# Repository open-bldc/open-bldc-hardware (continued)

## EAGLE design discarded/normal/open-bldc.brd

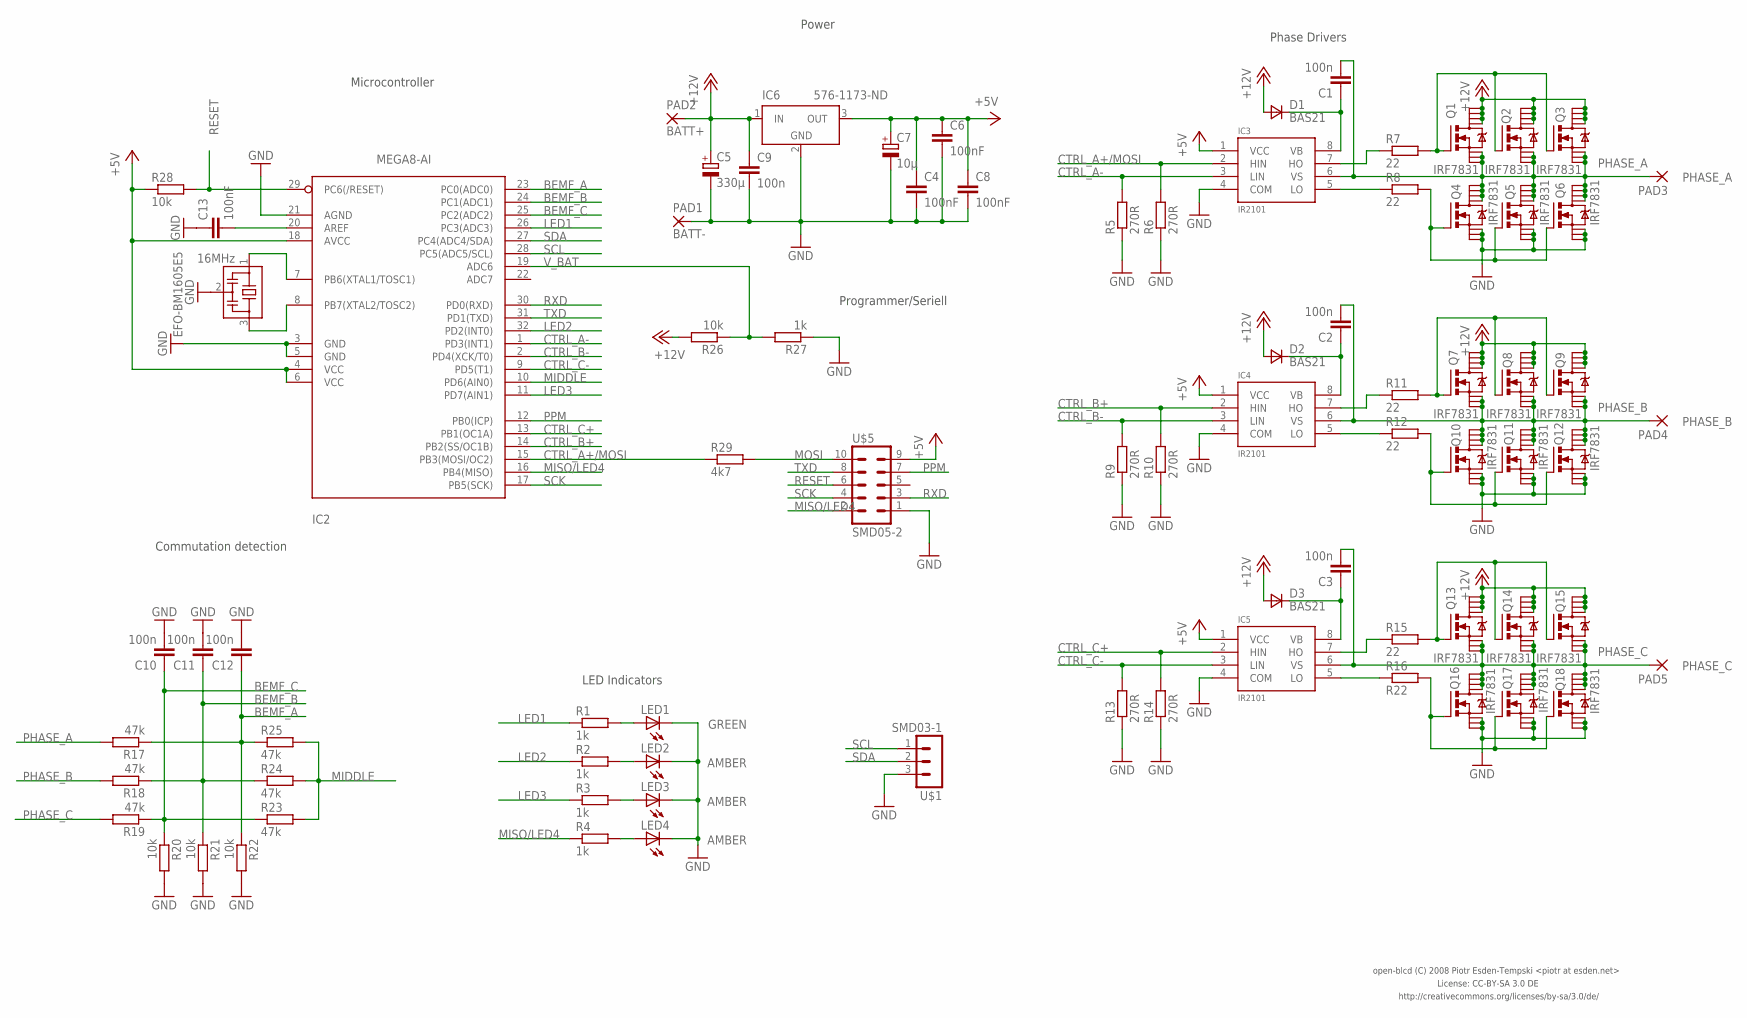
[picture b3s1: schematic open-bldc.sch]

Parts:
C1, C2, C3, C9, C10, C11, C12: 100n; C0603
C4, C6, C8, C13: 100nF; C0603
C5: 330µ; E3,5-8
C7: 10µ; D/7343-31R
D1, D2, D3: BAS21; SOT-23
EFO-BM1605E5: 16MHz; EFOBM
IC2: MEGA8-AI; TQFP32-08
IC3, IC4, IC5: IR2101; SO-8
IC6: 576-1173-ND; SOT223
LED1: GREEN; CHIP-LED0603
LED2, LED3, LED4: AMBER; CHIP-LED0603
PAD1: BATT-; SMD2,54-5,08
PAD2: BATT+; SMD2,54-5,08
PAD3: PHASE_A; SMD2,54-5,08
PAD4: PHASE_B; SMD2,54-5,08
PAD5: PHASE_C; SMD2,54-5,08
Q1, Q2, Q3, Q4, Q5, Q6, Q7, Q8, Q9, Q10, Q11, Q12, Q13, Q14, Q15, Q16, Q17, Q18: IRF7831; SO-08
R1, R2, R3, R4, R27: 1k; R0603
R5, R6, R9, R10, R13, R14: 270R; R0603
R7, R8, R11, R12, R15: 22; R0603
R16: R22; R0603
R17, R18, R19, R23, R24, R25: 47k; R0603
R20, R21, R22, R26, R28: 10k; R0603
R29: 4k7; R0603
U$1: SMD03-1
U$5: SMD05-2

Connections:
+5V: C4.1, C6.1, C7.+, C8.1, IC2.4 (VCC), IC2.6 (VCC), IC2.18 (AVCC), IC3.1 (VCC), IC4.1 (VCC), IC5.1 (VCC), IC6.3 (OUT), R28.1, U$5.9
+12V: C5.+, C9.1, D1.3 (A), D2.3 (A), D3.3 (A), IC6.1 (IN), PAD2.1, Q1.5 (D), Q1.6 (D), Q1.7 (D), Q1.8 (D), Q2.5 (D), Q2.6 (D), Q2.7 (D), Q2.8 (D), Q3.5 (D), Q3.6 (D), Q3.7 (D), Q3.8 (D), Q7.5 (D), Q7.6 (D), Q7.7 (D), Q7.8 (D), Q8.5 (D), Q8.6 (D), Q8.7 (D), Q8.8 (D), Q9.5 (D), Q9.6 (D), Q9.7 (D), Q9.8 (D), Q13.5 (D), Q13.6 (D), Q13.7 (D), Q13.8 (D), Q14.5 (D), Q14.6 (D), Q14.7 (D), Q14.8 (D), Q15.5 (D), Q15.6 (D), Q15.7 (D), Q15.8 (D), R26.2
BEMF_A: C12.1, IC2.23 (PC0(ADC0)), R17.1, R22.1, R25.1
BEMF_B: C11.1, IC2.24 (PC1(ADC1)), R18.1, R21.1, R24.1
BEMF_C: C10.1, IC2.25 (PC2(ADC2)), R19.1, R20.1, R23.1
CTRL_A+/MOSI: IC2.15 (PB3(MOSI/OC2)), IC3.2 (HIN), R6.2, R29.1
CTRL_A-: IC2.1 (PD3(INT1)), IC3.3 (LIN), R5.2
CTRL_B+: IC2.14 (PB2(SS/OC1B)), IC4.2 (HIN), R10.2
CTRL_B-: IC2.2 (PD4(XCK/T0)), IC4.3 (LIN), R9.2
CTRL_C+: IC2.13 (PB1(OC1A)), IC5.2 (HIN), R14.2
CTRL_C-: IC2.9 (PD5(T1)), IC5.3 (LIN), R13.2
GND: C4.2, C5.-, C6.2, C7.-, C8.2, C9.2, C10.2, C11.2, C12.2, C13.1, EFO-BM1605E5.2, IC2.3 (GND), IC2.5 (GND), IC2.21 (AGND), IC3.4 (COM), IC4.4 (COM), IC5.4 (COM), IC6.2 (GND), IC6.4 (GND), LED1.C, LED2.C, LED3.C, LED4.C, PAD1.1, Q4.1 (S), Q4.2 (S), Q4.3 (S), Q5.1 (S), Q5.2 (S), Q5.3 (S), Q6.1 (S), Q6.2 (S), Q6.3 (S), Q10.1 (S), Q10.2 (S), Q10.3 (S), Q11.1 (S), Q11.2 (S), Q11.3 (S), Q12.1 (S), Q12.2 (S), Q12.3 (S), Q16.1 (S), Q16.2 (S), Q16.3 (S), Q17.1 (S), Q17.2 (S), Q17.3 (S), Q18.1 (S), Q18.2 (S), Q18.3 (S), R5.1, R6.1, R9.1, R10.1, R13.1, R14.1, R20.2, R21.2, R22.2, R27.1, U$1.3, U$5.1
LED1: IC2.26 (PC3(ADC3)), R1.1
LED2: IC2.32 (PD2(INT0)), R2.1
LED3: IC2.11 (PD7(AIN1)), R3.1
MIDDLE: IC2.10 (PD6(AIN0)), R23.2, R24.2, R25.2
MISO/LED4: IC2.16 (PB4(MISO)), R4.1, U$5.2
MOSI: R29.2, U$5.10
unnamed: IC4.7 (HO), R11.1
unnamed: IC3.7 (HO), R7.1
unnamed: LED1.A, R1.2
unnamed: LED2.A, R2.2
unnamed: LED3.A, R3.2
unnamed: C13.2, IC2.20 (AREF)
unnamed: IC3.5 (LO), R8.1
unnamed: EFO-BM1605E5.1, IC2.7 (PB6(XTAL1/TOSC1))
unnamed: EFO-BM1605E5.3, IC2.8 (PB7(XTAL2/TOSC2))
unnamed: LED4.A, R4.2
unnamed: Q1.4 (G), Q2.4 (G), Q3.4 (G), R7.2
unnamed: C1.1, D1.1 (C), IC3.8 (VB)
unnamed: IC4.5 (LO), R12.1
unnamed: Q7.4 (G), Q8.4 (G), Q9.4 (G), R11.2
unnamed: Q4.4 (G), Q5.4 (G), Q6.4 (G), R8.2
unnamed: C2.1, D2.1 (C), IC4.8 (VB)
unnamed: Q10.4 (G), Q11.4 (G), Q12.4 (G), R12.2
unnamed: IC5.7 (HO), R15.1
unnamed: IC5.5 (LO), R16.1
unnamed: Q13.4 (G), Q14.4 (G), Q15.4 (G), R15.2
unnamed: C3.1, D3.1 (C), IC5.8 (VB)
unnamed: Q16.4 (G), Q17.4 (G), Q18.4 (G), R16.2
PHASE_A: C1.2, IC3.6 (VS), PAD3.1, Q1.1 (S), Q1.2 (S), Q1.3 (S), Q2.1 (S), Q2.2 (S), Q2.3 (S), Q3.1 (S), Q3.2 (S), Q3.3 (S), Q4.5 (D), Q4.6 (D), Q4.7 (D), Q4.8 (D), Q5.5 (D), Q5.6 (D), Q5.7 (D), Q5.8 (D), Q6.5 (D), Q6.6 (D), Q6.7 (D), Q6.8 (D), R17.2
PHASE_B: C2.2, IC4.6 (VS), PAD4.1, Q7.1 (S), Q7.2 (S), Q7.3 (S), Q8.1 (S), Q8.2 (S), Q8.3 (S), Q9.1 (S), Q9.2 (S), Q9.3 (S), Q10.5 (D), Q10.6 (D), Q10.7 (D), Q10.8 (D), Q11.5 (D), Q11.6 (D), Q11.7 (D), Q11.8 (D), Q12.5 (D), Q12.6 (D), Q12.7 (D), Q12.8 (D), R18.2
PHASE_C: C3.2, IC5.6 (VS), PAD5.1, Q13.1 (S), Q13.2 (S), Q13.3 (S), Q14.1 (S), Q14.2 (S), Q14.3 (S), Q15.1 (S), Q15.2 (S), Q15.3 (S), Q16.5 (D), Q16.6 (D), Q16.7 (D), Q16.8 (D), Q17.5 (D), Q17.6 (D), Q17.7 (D), Q17.8 (D), Q18.5 (D), Q18.6 (D), Q18.7 (D), Q18.8 (D), R19.2
PPM: IC2.12 (PB0(ICP)), U$5.7
RESET: IC2.29 (PC6(/RESET)), R28.2, U$5.6
RXD: IC2.30 (PD0(RXD)), U$5.3
SCK: IC2.17 (PB5(SCK)), U$5.4
SCL: IC2.28 (PC5(ADC5/SCL)), U$1.1
SDA: IC2.27 (PC4(ADC4/SDA)), U$1.2
TXD: IC2.31 (PD1(TXD)), U$5.8
V_BAT: IC2.19 (ADC6), R26.1, R27.2

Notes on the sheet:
Programmer/Seriell
Power
Microcontroller
Phase Drivers
License: CC-BY-SA 3.0 DE
http://creativecommons.org/licenses/by-sa/3.0/de/
LED Indicators
Commutation detection
open-blcd (C) 2008 Piotr Esden-Tempski <piotr at esden.net>

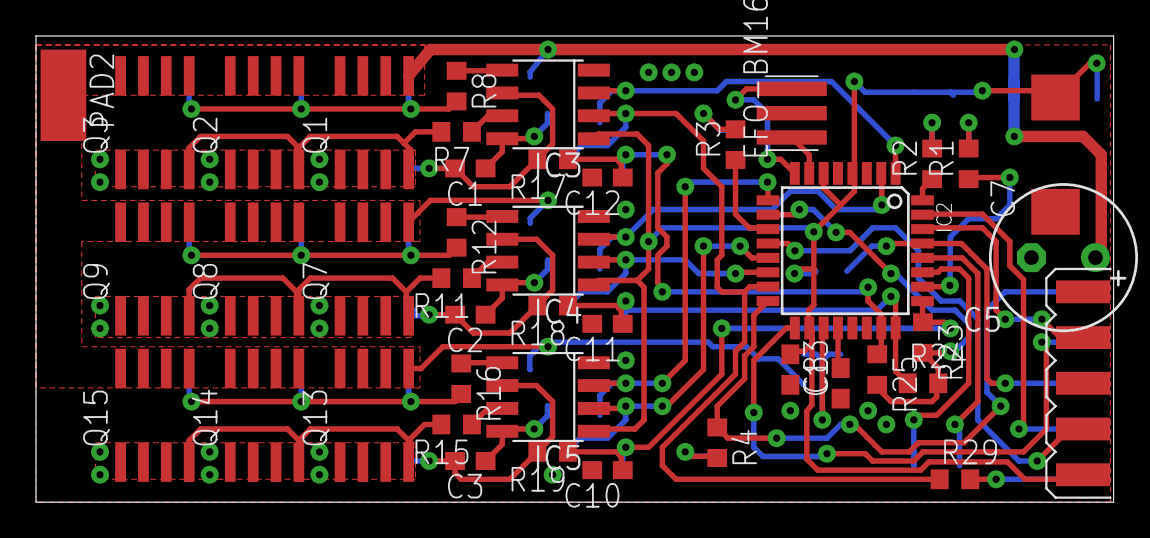
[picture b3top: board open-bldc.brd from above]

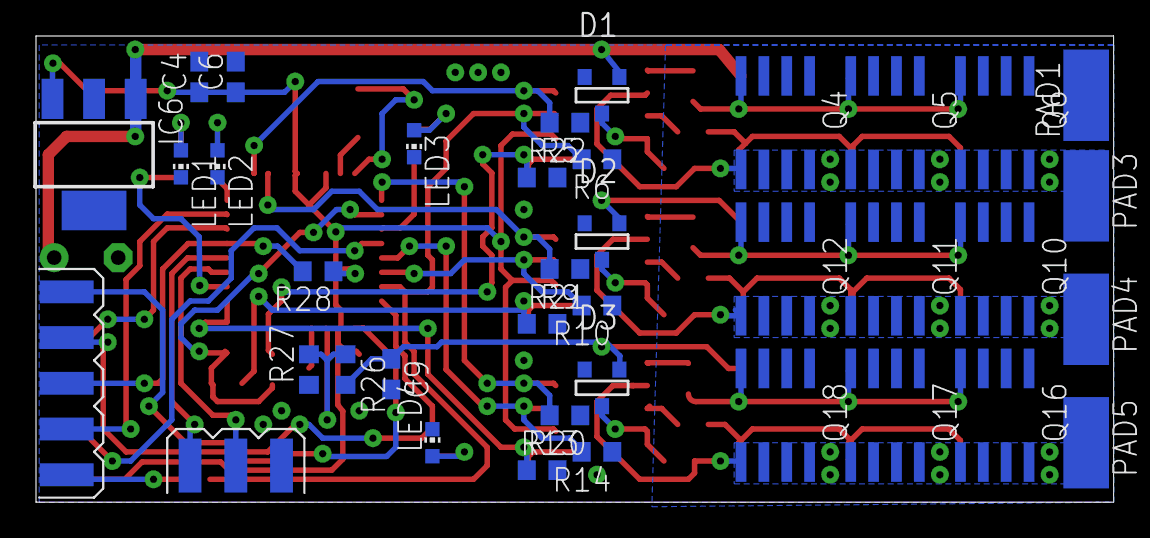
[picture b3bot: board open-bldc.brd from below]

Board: 2 copper layers, 59.9 x 25.9 mm, 80 parts (38 on the bottom side), 51 nets.

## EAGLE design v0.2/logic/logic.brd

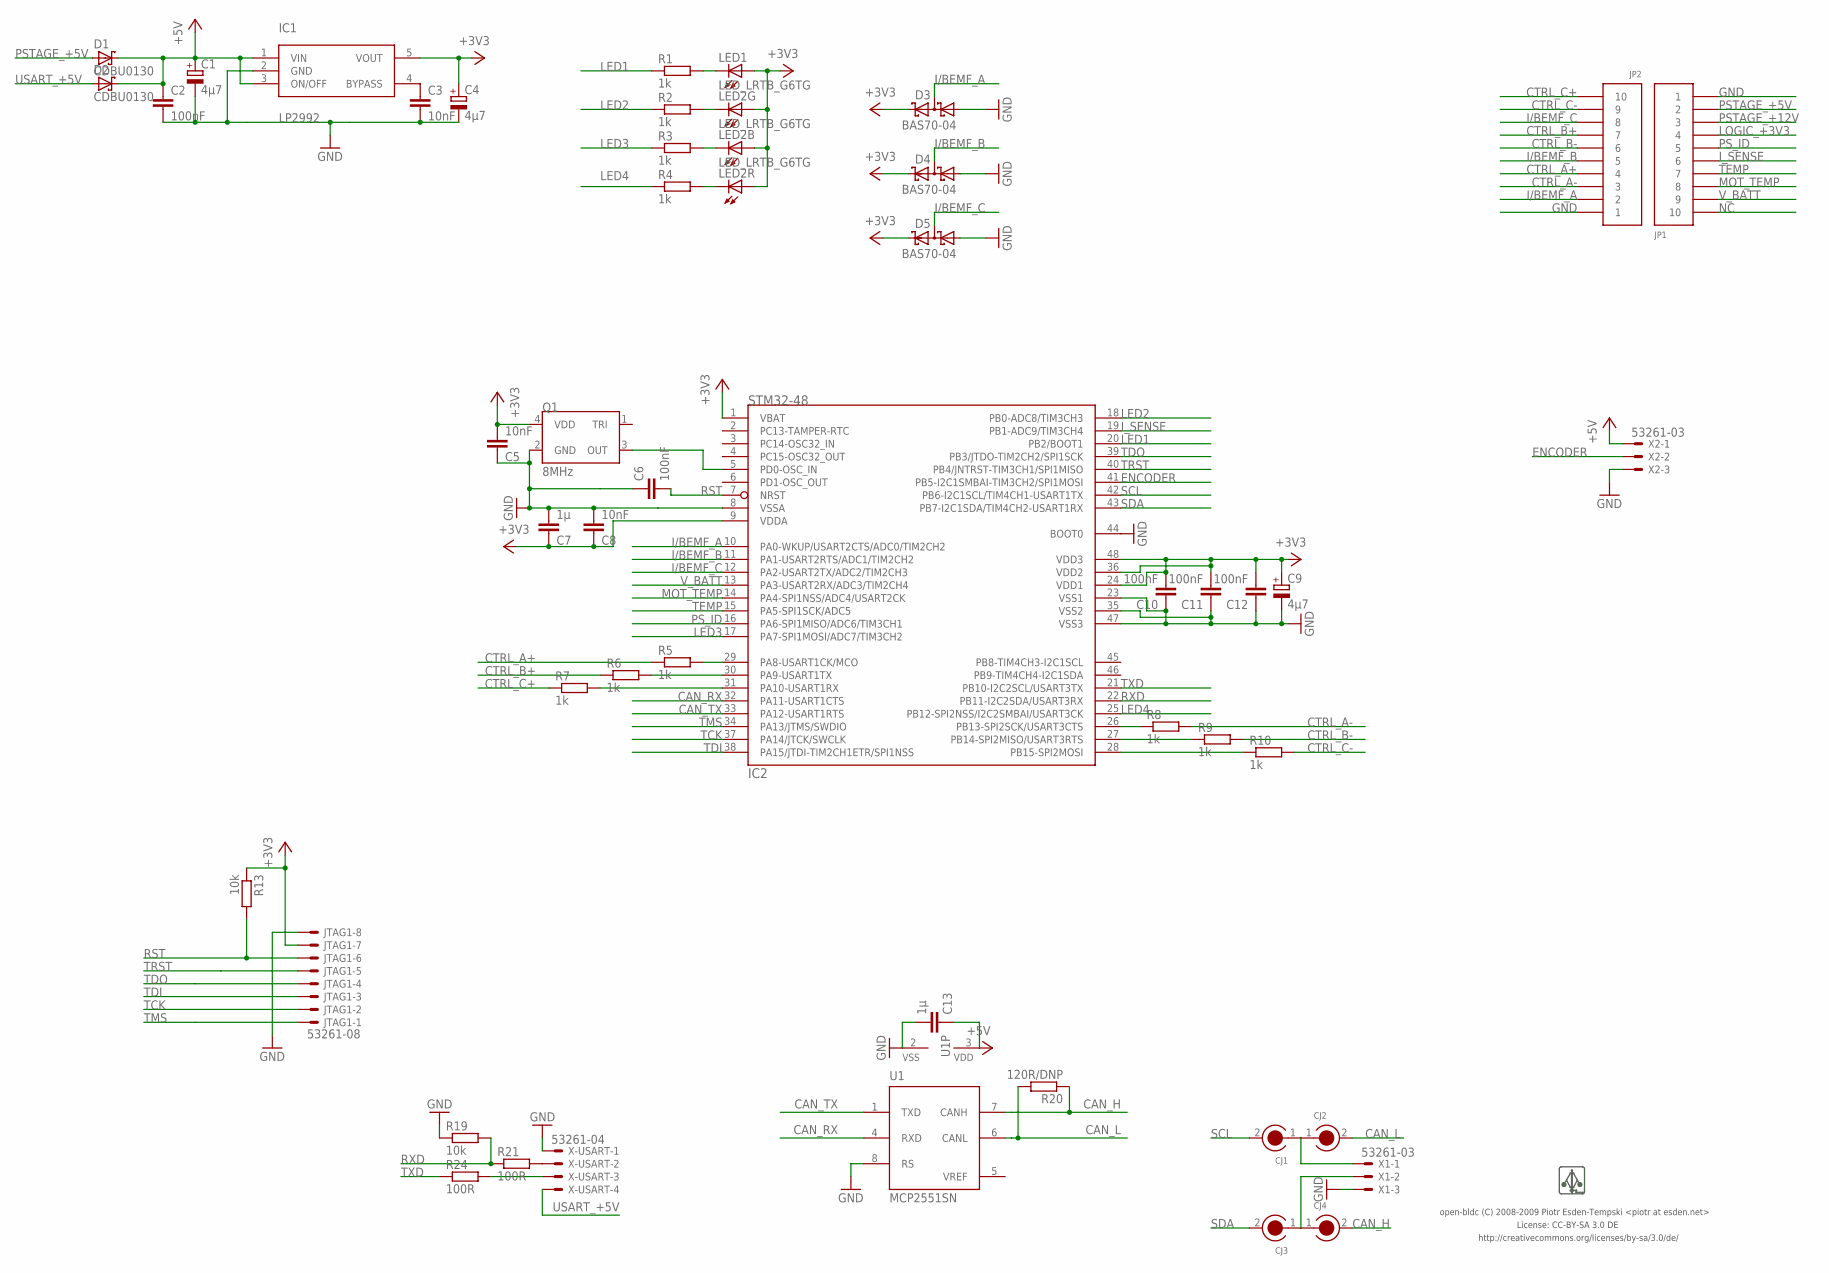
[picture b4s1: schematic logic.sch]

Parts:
C1, C4, C9: 4µ7; A/3216-18R
C2, C6, C10, C11, C12: 100nF; C0603
C3, C5, C8: 10nF; C0603
C7, C13: 1µ; C0603
CJ1, CJ2, CJ3, CJ4: CIRC_JMP
D1, D2: CDBU0130; SOD523
D3, D4, D5: BAS70-04; SOT23
IC1: LP2992; SOT23-5
IC2: STM32-48; LQFP48
JP1, JP2: PIN_HDR_1.27MM_10
JTAG1: 53261-08
LED1: AMBER; CHIP-LED0603
LED2: LED_LRTB_G6TG; PLCC6
Q1: 8MHz; ASE_OSCILLATOR
R1, R2, R3, R4, R5, R6, R7, R8, R9, R10: 1k; R0603
R13, R19: 10k; R0603
R20: 120R/DNP; R0603
R21, R24: 100R; R0603
U1: MCP2551SN; SO-08
U$1: LOGO
X1, X2: 53261-03
X-USART: 53261-04

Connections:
+3V3: C4.+, C5.2, C7.1, C8.1, C9.+, C10.2, C11.2, C12.2, D3.2 (C2), D4.2 (C2), D5.2 (C2), IC1.5 (VOUT), IC2.1 (VBAT), IC2.9 (VDDA), IC2.24 (VDD1), IC2.36 (VDD2), IC2.48 (VDD3), JTAG1.7, LED1.A, LED2.A1 (A), LED2.A2 (A), LED2.A3 (A), Q1.4 (VDD), R13.1
+5V: C1.+, C2.1, C13.1, D1.C, D2.C, IC1.1 (VIN), IC1.3 (ON/OFF), U1.3 (VDD), X2.1
CAN_H: CJ4.2, R20.1, U1.7 (CANH)
CAN_L: CJ2.2, R20.2, U1.6 (CANL)
CAN_RX: IC2.32 (PA11-USART1CTS), U1.4 (RXD)
CAN_TX: IC2.33 (PA12-USART1RTS), U1.1 (TXD)
CTRL_A+: JP2.P$4 (4), R5.1
CTRL_A-: JP2.P$3 (3), R8.2
CTRL_B+: JP2.P$7 (7), R6.1
CTRL_B-: JP2.P$6 (6), R9.2
CTRL_C+: JP2.P$10 (10), R7.1
CTRL_C-: JP2.P$9 (9), R10.2
ENCODER: IC2.41 (PB5-I2C1SMBAI-TIM3CH2/SPI1MOSI), X2.2
GND: C1.-, C2.2, C3.2, C4.-, C5.1, C6.1, C7.2, C8.2, C9.-, C10.1, C11.1, C12.1, C13.2, D3.1 (A1), D4.1 (A1), D5.1 (A1), IC1.2 (GND), IC2.8 (VSSA), IC2.23 (VSS1), IC2.35 (VSS2), IC2.44 (BOOT0), IC2.47 (VSS3), JP1.P$1 (1), JP2.P$1 (1), JTAG1.8, Q1.2 (GND), R19.1, U1.2 (VSS), U1.8 (RS), X1.3, X2.3, X-USART.1
I/BEMF_A: D3.3 (C1A2), IC2.10 (PA0-WKUP/USART2CTS/ADC0/TIM2CH2), JP2.P$2 (2)
I/BEMF_B: D4.3 (C1A2), IC2.11 (PA1-USART2RTS/ADC1/TIM2CH2), JP2.P$5 (5)
I/BEMF_C: D5.3 (C1A2), IC2.12 (PA2-USART2TX/ADC2/TIM2CH3), JP2.P$8 (8)
I_SENSE: IC2.19 (PB1-ADC9/TIM3CH4), JP1.P$6 (6)
LED1: IC2.20 (PB2/BOOT1), R1.1
LED2: IC2.18 (PB0-ADC8/TIM3CH3), R2.1
LED3: IC2.17 (PA7-SPI1MOSI/ADC7/TIM3CH2), R3.1
LED4: IC2.25 (PB12-SPI2NSS/I2C2SMBAI/USART3CK), R4.1
LOGIC_+3V3: JP1.P$4 (4)
MOT_TEMP: IC2.14 (PA4-SPI1NSS/ADC4/USART2CK), JP1.P$8 (8)
unnamed: CJ3.1, CJ4.1, X1.2
unnamed: CJ1.1, CJ2.1, X1.1
unnamed: LED1.C, R1.2
unnamed: LED2.C1 (C), R4.2
unnamed: LED2.C3 (C), R3.2
unnamed: R21.2, X-USART.2
unnamed: LED2.C2 (C), R2.2
unnamed: R24.2, X-USART.3
unnamed: C3.1, IC1.4 (BYPASS)
unnamed: IC2.26 (PB13-SPI2SCK/USART3CTS), R8.1
unnamed: IC2.27 (PB14-SPI2MISO/USART3RTS), R9.1
unnamed: IC2.28 (PB15-SPI2MOSI), R10.1
unnamed: IC2.5 (PD0-OSC_IN), Q1.3 (OUT)
unnamed: IC2.29 (PA8-USART1CK/MCO), R5.2
unnamed: IC2.30 (PA9-USART1TX), R6.2
unnamed: IC2.31 (PA10-USART1RX), R7.2
NC: JP1.P$10 (10)
PSTAGE_+5V: D1.A, JP1.P$2 (2)
PSTAGE_+12V: JP1.P$3 (3)
PS_ID: IC2.16 (PA6-SPI1MISO/ADC6/TIM3CH1), JP1.P$5 (5)
RST: C6.2, IC2.7 (NRST), JTAG1.6, R13.2
RXD: IC2.22 (PB11-I2C2SDA/USART3RX), R19.2, R21.1
SCL: CJ1.2, IC2.42 (PB6-I2C1SCL/TIM4CH1-USART1TX)
SDA: CJ3.2, IC2.43 (PB7-I2C1SDA/TIM4CH2-USART1RX)
TCK: IC2.37 (PA14/JTCK/SWCLK), JTAG1.2
TDI: IC2.38 (PA15/JTDI-TIM2CH1ETR/SPI1NSS), JTAG1.3
TDO: IC2.39 (PB3/JTDO-TIM2CH2/SPI1SCK), JTAG1.4
TEMP: IC2.15 (PA5-SPI1SCK/ADC5), JP1.P$7 (7)
TMS: IC2.34 (PA13/JTMS/SWDIO), JTAG1.1
TRST: IC2.40 (PB4/JNTRST-TIM3CH1/SPI1MISO), JTAG1.5
TXD: IC2.21 (PB10-I2C2SCL/USART3TX), R24.1
USART_+5V: D2.A, X-USART.4
VREF: U1.5 (VREF)
V_BATT: IC2.13 (PA3-USART2RX/ADC3/TIM2CH4), JP1.P$9 (9)

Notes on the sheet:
License: CC-BY-SA 3.0 DE
http://creativecommons.org/licenses/by-sa/3.0/de/
open-bldc (C) 2008-2009 Piotr Esden-Tempski <piotr at esden.net>

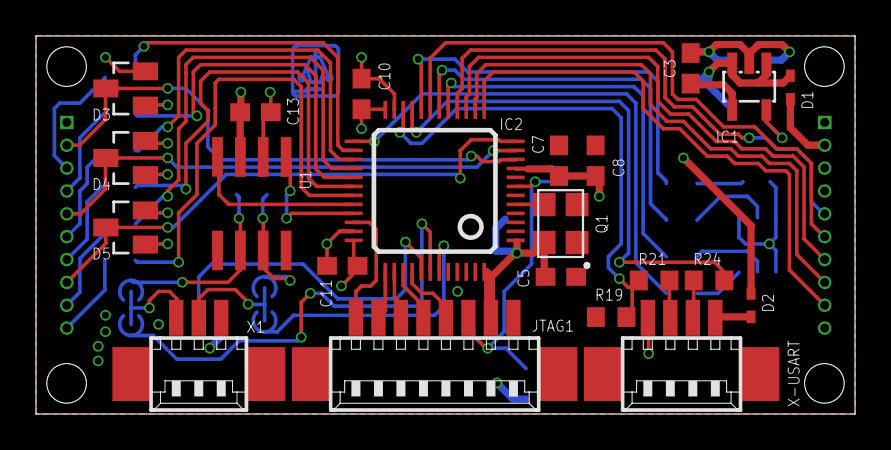
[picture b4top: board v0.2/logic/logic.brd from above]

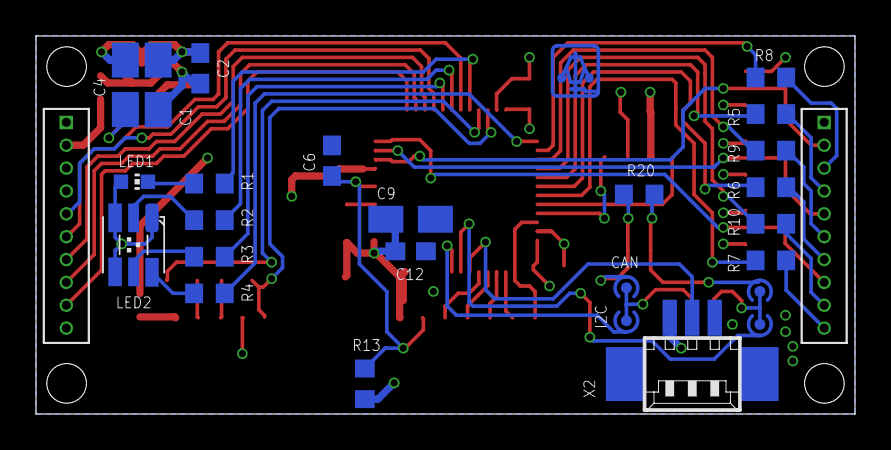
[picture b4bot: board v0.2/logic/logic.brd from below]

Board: 4 copper layers, 45.5 x 21.0 mm, 50 parts (28 on the bottom side), 54 nets.

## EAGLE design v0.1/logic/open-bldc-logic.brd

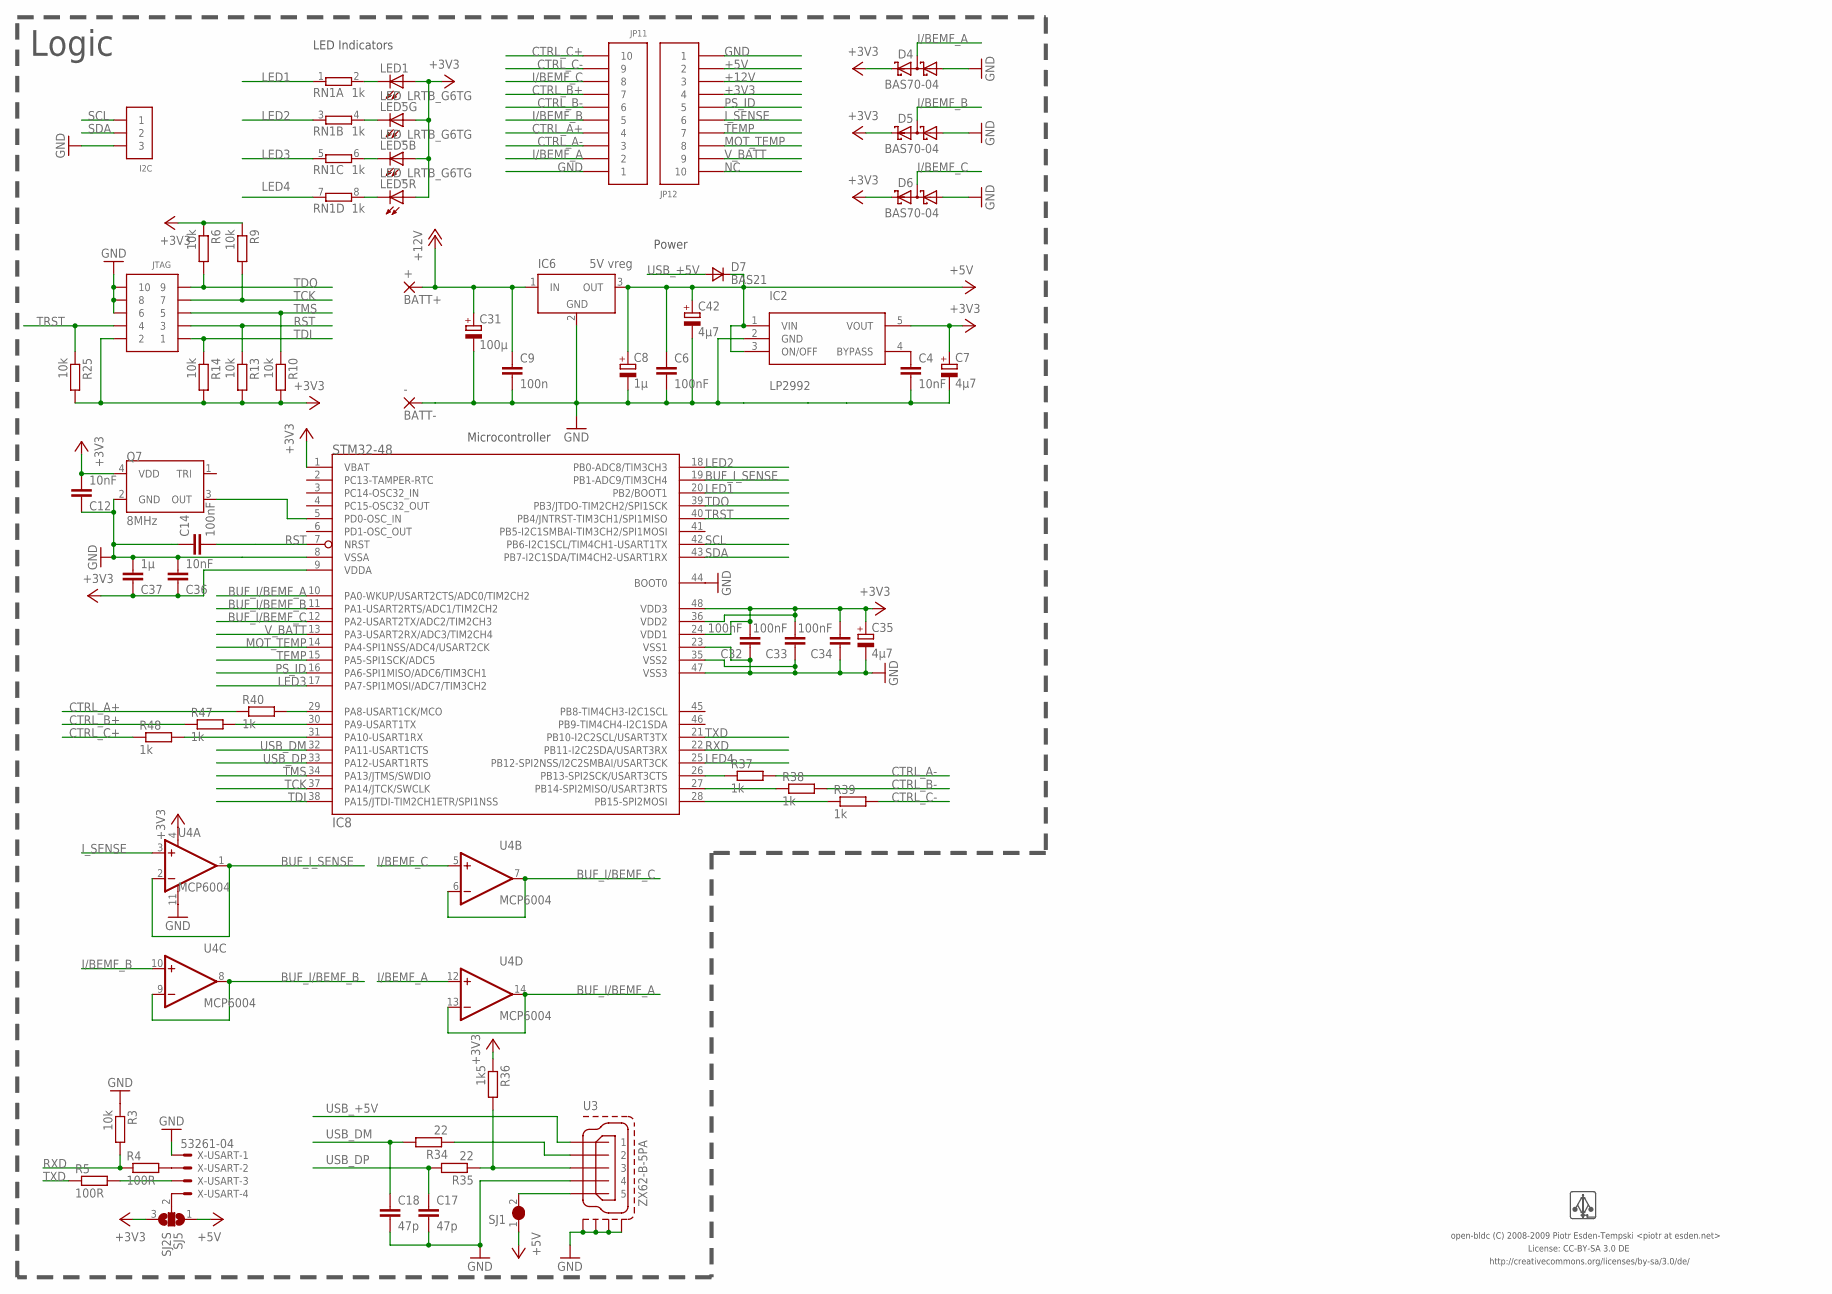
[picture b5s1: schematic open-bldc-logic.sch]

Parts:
+: BATT+; SMD2,54-5,08
-: BATT-; SMD2,54-5,08
C4, C12, C36: 10nF; C0603
C6, C14, C32, C33, C34: 100nF; C0603
C7, C35, C42: 4µ7; A/3216-18R
C8: 1µ; A/3216-18R
C9: 100n; C0603
C17, C18: 47p; C0603
C31: 100µ; D/7343-31R
C37: 1µ; C0603
D4, D5, D6: BAS70-04; SOT23
D7: BAS21; SOT-23
I2C: PIN_HDR_EDG_1.27MM_3-1
IC2: LP2992; SOT23-5
IC6: 5V vreg; SOT223
IC8: STM32-48; LQFP48
JP11, JP12: PIN_HDR_1.27MM_10
JTAG: PIN_HDR_EDG_1.27MM_5-2
LED1: AMBER; CHIP-LED0603
LED5: LED_LRTB_G6TG; PLCC6
Q7: 8MHz; ASE_OSCILLATOR
R3, R6, R9, R10, R13, R14, R25: 10k; R0603
R4, R5: 100R; R0603
R34, R35: 22; R0603
R36: 1k5; R0603
R37, R38, R39, R40, R47, R48: 1k; R0603
RN1: 1k; R4N1206
SJ1: SJ1S
SJ5: SJ2S
U3: ZX62-B-5PA
U4: MCP6004; TSSOP_14
X-USART: 53261-04

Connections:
+3V3: C7.+, C12.2, C32.2, C33.2, C34.2, C35.+, C36.1, C37.1, D4.2 (C2), D5.2 (C2), D6.2 (C2), IC2.5 (VOUT), IC8.1 (VBAT), IC8.9 (VDDA), IC8.24 (VDD1), IC8.36 (VDD2), IC8.48 (VDD3), JP12.P$4 (4), JTAG.P$2 (2), LED1.A, LED5.A1 (A), LED5.A2 (A), LED5.A3 (A), Q7.4 (VDD), R6.1, R9.1, R10.2, R13.2, R14.2, R25.2, R36.1, SJ5.3, U4.4 (V+)
+5V: C6.1, C8.+, C42.+, D7.1 (C), IC2.1 (VIN), IC2.3 (ON/OFF), IC6.3 (OUT), JP12.P$2 (2), SJ1.1, SJ5.1
+12V: +.1, C9.1, C31.+, IC6.1 (IN), JP12.P$3 (3)
BUF_I/BEMF_A: IC8.10 (PA0-WKUP/USART2CTS/ADC0/TIM2CH2), U4.13 (-IN), U4.14 (OUT)
BUF_I/BEMF_B: IC8.11 (PA1-USART2RTS/ADC1/TIM2CH2), U4.8 (OUT), U4.9 (-IN)
BUF_I/BEMF_C: IC8.12 (PA2-USART2TX/ADC2/TIM2CH3), U4.6 (-IN), U4.7 (OUT)
BUF_I_SENSE: IC8.19 (PB1-ADC9/TIM3CH4), U4.1 (OUT), U4.2 (-IN)
CTRL_A+: JP11.P$4 (4), R40.1
CTRL_A-: JP11.P$3 (3), R37.2
CTRL_B+: JP11.P$7 (7), R47.1
CTRL_B-: JP11.P$6 (6), R38.2
CTRL_C+: JP11.P$10 (10), R48.1
CTRL_C-: JP11.P$9 (9), R39.2
GND: -.1, C4.2, C6.2, C7.-, C8.-, C9.2, C12.1, C14.1, C17.2, C18.2, C31.-, C32.1, C33.1, C34.1, C35.-, C36.2, C37.2, C42.-, D4.1 (A1), D5.1 (A1), D6.1 (A1), I2C.P$3 (3), IC2.2 (GND), IC6.2 (GND), IC6.4 (GND), IC8.8 (VSSA), IC8.23 (VSS1), IC8.35 (VSS2), IC8.44 (BOOT0), IC8.47 (VSS3), JP11.P$1 (1), JP12.P$1 (1), JTAG.P$6 (6), JTAG.P$8 (8), JTAG.P$10 (10), Q7.2 (GND), R3.1, U3.GND_LEFT (S1), U3.GND_RIGHT (S2), U3.GND_UP_LEFT (S3), U3.GND_UP_RIGHT (S4), U3.PIN_4 (4), U4.11 (V-), X-USART.1
I/BEMF_A: D4.3 (C1A2), JP11.P$2 (2), U4.12 (+IN)
I/BEMF_B: D5.3 (C1A2), JP11.P$5 (5), U4.10 (+IN)
I/BEMF_C: D6.3 (C1A2), JP11.P$8 (8), U4.5 (+IN)
I_SENSE: JP12.P$6 (6), U4.3 (+IN)
LED1: IC8.20 (PB2/BOOT1), RN1.1
LED2: IC8.18 (PB0-ADC8/TIM3CH3), RN1.3 (1)
LED3: IC8.17 (PA7-SPI1MOSI/ADC7/TIM3CH2), RN1.5 (1)
LED4: IC8.25 (PB12-SPI2NSS/I2C2SMBAI/USART3CK), RN1.7 (1)
MOT_TEMP: IC8.14 (PA4-SPI1NSS/ADC4/USART2CK), JP12.P$8 (8)
unnamed: IC8.29 (PA8-USART1CK/MCO), R40.2
unnamed: LED5.C1 (C), RN1.8 (2)
unnamed: LED1.C, RN1.2
unnamed: LED5.C3 (C), RN1.6 (2)
unnamed: LED5.C2 (C), RN1.4 (2)
unnamed: IC8.26 (PB13-SPI2SCK/USART3CTS), R37.1
unnamed: SJ5.2, X-USART.4
unnamed: R4.2, X-USART.2
unnamed: R5.2, X-USART.3
unnamed: C4.1, IC2.4 (BYPASS)
unnamed: R34.1, U3.PIN_2 (2)
unnamed: SJ1.2, U3.PIN_5 (5)
unnamed: R35.1, R36.2, U3.PIN_3 (3)
unnamed: IC8.27 (PB14-SPI2MISO/USART3RTS), R38.1
unnamed: IC8.28 (PB15-SPI2MOSI), R39.1
unnamed: IC8.5 (PD0-OSC_IN), Q7.3 (OUT)
unnamed: IC8.30 (PA9-USART1TX), R47.2
unnamed: IC8.31 (PA10-USART1RX), R48.2
NC: JP12.P$10 (10)
PS_ID: IC8.16 (PA6-SPI1MISO/ADC6/TIM3CH1), JP12.P$5 (5)
RST: C14.2, IC8.7 (NRST), JTAG.P$3 (3), R13.1
RXD: IC8.22 (PB11-I2C2SDA/USART3RX), R3.2, R4.1
SCL: I2C.P$1 (1), IC8.42 (PB6-I2C1SCL/TIM4CH1-USART1TX)
SDA: I2C.P$2 (2), IC8.43 (PB7-I2C1SDA/TIM4CH2-USART1RX)
TCK: IC8.37 (PA14/JTCK/SWCLK), JTAG.P$7 (7), R9.2
TDI: IC8.38 (PA15/JTDI-TIM2CH1ETR/SPI1NSS), JTAG.P$1 (1), R14.1
TDO: IC8.39 (PB3/JTDO-TIM2CH2/SPI1SCK), JTAG.P$9 (9), R6.2
TEMP: IC8.15 (PA5-SPI1SCK/ADC5), JP12.P$7 (7)
TMS: IC8.34 (PA13/JTMS/SWDIO), JTAG.P$5 (5), R10.1
TRST: IC8.40 (PB4/JNTRST-TIM3CH1/SPI1MISO), JTAG.P$4 (4), R25.1
TXD: IC8.21 (PB10-I2C2SCL/USART3TX), R5.1
USB_+5V: D7.3 (A), U3.PIN_1 (1)
USB_DM: C18.1, IC8.32 (PA11-USART1CTS), R34.2
USB_DP: C17.1, IC8.33 (PA12-USART1RTS), R35.2
V_BATT: IC8.13 (PA3-USART2RX/ADC3/TIM2CH4), JP12.P$9 (9)

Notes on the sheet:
Power
Microcontroller
License: CC-BY-SA 3.0 DE
http://creativecommons.org/licenses/by-sa/3.0/de/
LED Indicators
open-bldc (C) 2008-2009 Piotr Esden-Tempski <piotr at esden.net>
Logic

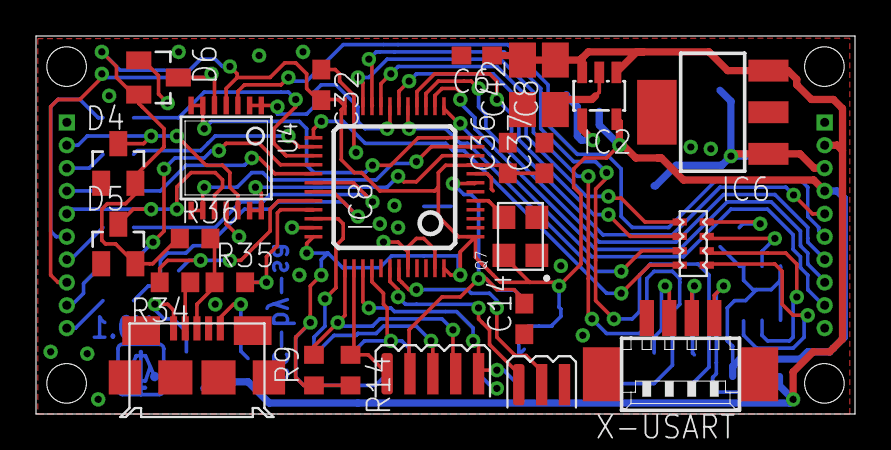
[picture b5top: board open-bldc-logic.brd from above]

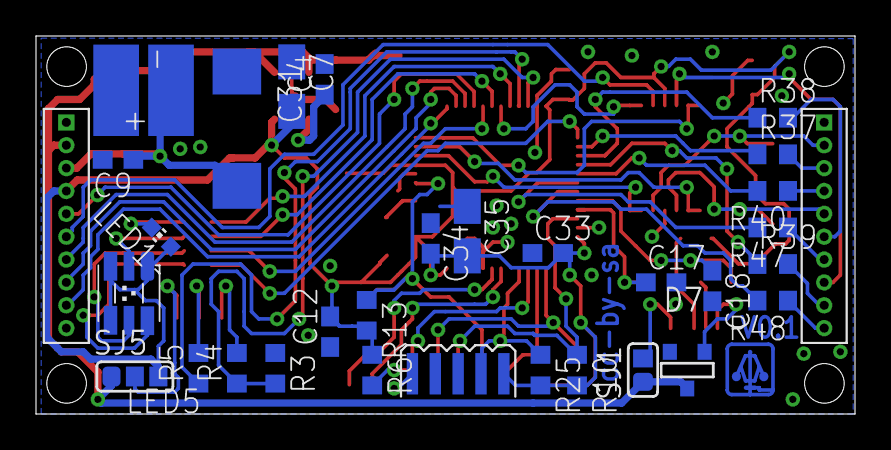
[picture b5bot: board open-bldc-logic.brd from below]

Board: 2 copper layers, 45.5 x 21.0 mm, 57 parts (32 on the bottom side), 57 nets.

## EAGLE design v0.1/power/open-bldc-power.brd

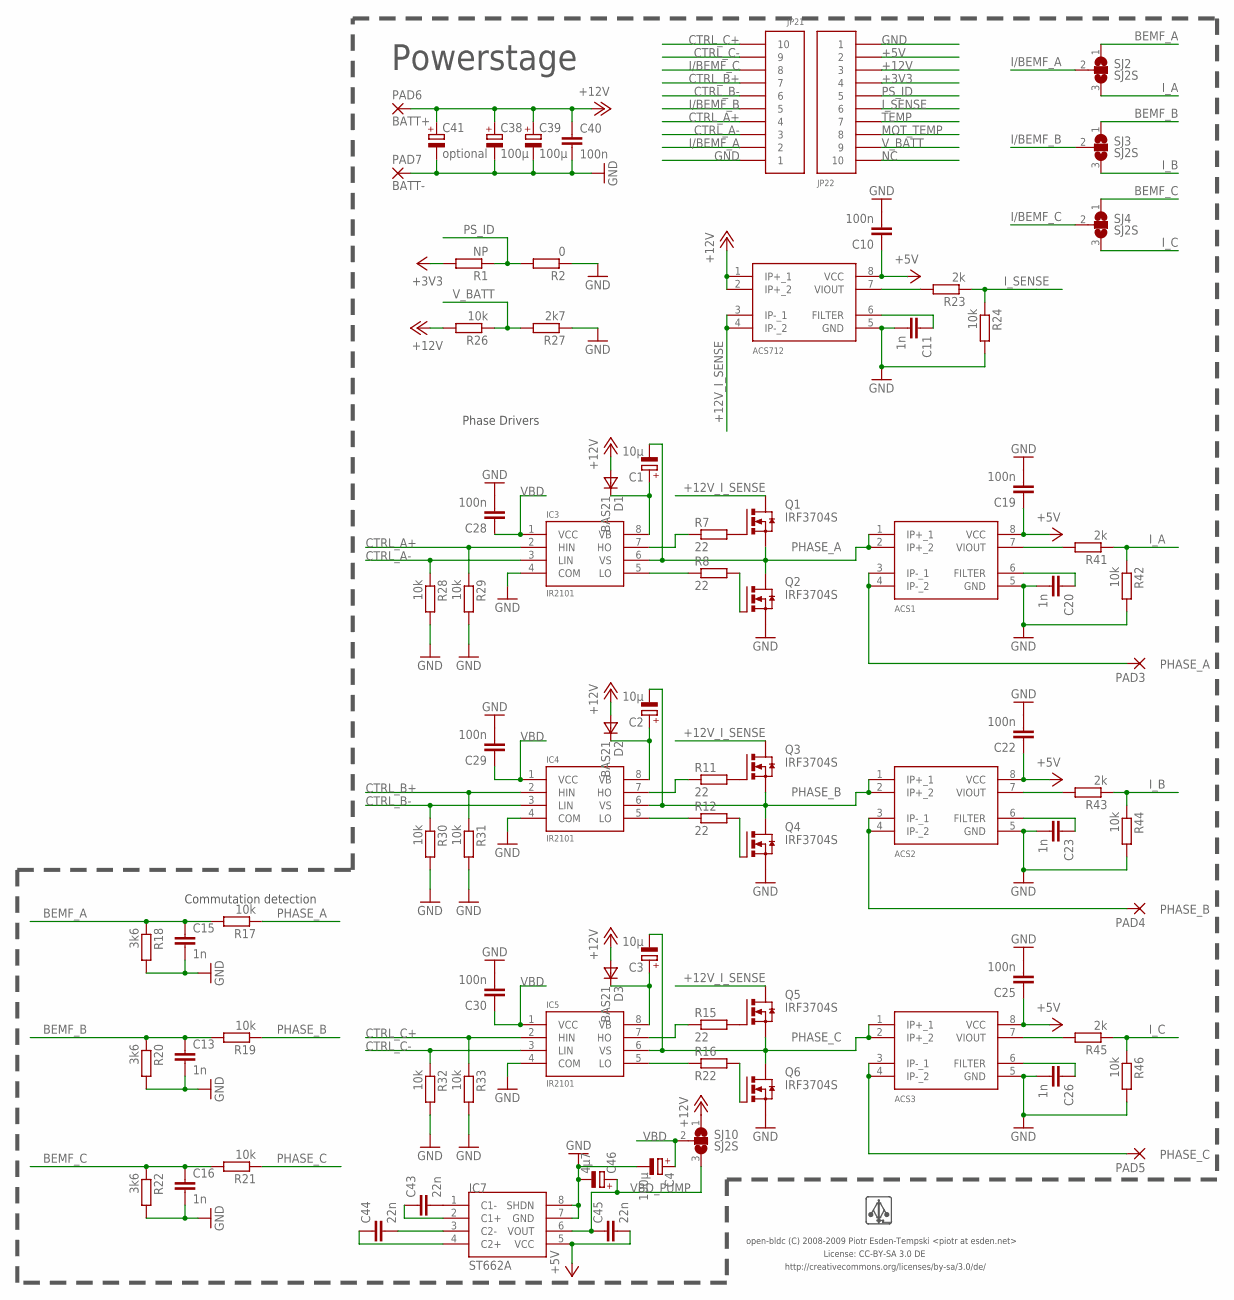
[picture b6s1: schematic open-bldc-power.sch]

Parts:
ACS1, ACS2, ACS3, ACS712: ACS712; SO8
C1, C2, C3: 10µ; A/3216-18R
C4, C38, C39: 100µ; D/7343-31R
C10, C19, C22, C25, C28, C29, C30, C40: 100n; C0603
C11, C13, C15, C16, C20, C23, C26: 1n; C0603
C41: optional; E5-6
C43, C44, C45: 22n; C0603
C46: 4µ7; A/3216-18R
D1, D2, D3: BAS21; SOT-23
IC3, IC4, IC5: IR2101; SO-8
IC7: ST662A; SO8
JP21, JP22: PIN_HDR_1.27MM_10
PAD3: PHASE_A; SMD2,54-5,08
PAD4: PHASE_B; SMD2,54-5,08
PAD5: PHASE_C; SMD2,54-5,08
PAD6: BATT+; SMD2,54-5,08
PAD7: BATT-; SMD2,54-5,08
Q1, Q2, Q3, Q4, Q5, Q6: IRF3704S; D2PACK
R1: NP; R0603
R2: 0; R0603
R7, R8, R11, R12, R15: 22; R0603
R16: R22; R0603
R17, R19, R21, R24, R26, R28, R29, R30, R31, R32, R33, R42, R44, R46: 10k; R0603
R18, R20, R22: 3k6; R0603
R23, R41, R43, R45: 2k; R0603
R27: 2k7; R0603
SJ2, SJ3, SJ4, SJ10: SJ2S

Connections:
+3V3: JP22.P$4 (4), R1.2
+5V: ACS1.8 (VCC), ACS2.8 (VCC), ACS3.8 (VCC), ACS712.8 (VCC), C10.1, C19.1, C22.1, C25.1, C45.2, IC7.5 (VCC), JP22.P$2 (2)
+12V: ACS712.1 (IP+_1), ACS712.2 (IP+_2), C38.+, C39.+, C40.1, C41.+, D1.3 (A), D2.3 (A), D3.3 (A), JP22.P$3 (3), PAD6.1, R26.2, SJ10.1
+12V_I_SENSE: ACS712.3 (IP-_1), ACS712.4 (IP-_2), Q1.2 (D), Q3.2 (D), Q5.2 (D)
BEMF_A: C15.1, R17.2, R18.1, SJ2.1
BEMF_B: C13.1, R19.2, R20.1, SJ3.1
BEMF_C: C16.1, R21.2, R22.1, SJ4.1
CTRL_A+: IC3.2 (HIN), JP21.P$4 (4), R29.1
CTRL_A-: IC3.3 (LIN), JP21.P$3 (3), R28.1
CTRL_B+: IC4.2 (HIN), JP21.P$7 (7), R31.1
CTRL_B-: IC4.3 (LIN), JP21.P$6 (6), R30.1
CTRL_C+: IC5.2 (HIN), JP21.P$10 (10), R33.1
CTRL_C-: IC5.3 (LIN), JP21.P$9 (9), R32.1
GND: ACS1.5 (GND), ACS2.5 (GND), ACS3.5 (GND), ACS712.5 (GND), C4.-, C10.2, C11.2, C13.2, C15.2, C16.2, C19.2, C20.2, C22.2, C23.2, C25.2, C26.2, C28.2, C29.2, C30.2, C38.-, C39.-, C40.2, C41.-, C46.-, IC3.4 (COM), IC4.4 (COM), IC5.4 (COM), IC7.7 (GND), IC7.8 (SHDN), JP21.P$1 (1), JP22.P$1 (1), PAD7.1, Q2.3 (S), Q4.3 (S), Q6.3 (S), R2.1, R18.2, R20.2, R22.2, R24.2, R27.1, R28.2, R29.2, R30.2, R31.2, R32.2, R33.2, R42.2, R44.2, R46.2
I/BEMF_A: JP21.P$2 (2), SJ2.2
I/BEMF_B: JP21.P$5 (5), SJ3.2
I/BEMF_C: JP21.P$8 (8), SJ4.2
I_A: R41.1, R42.1, SJ2.3
I_B: R43.1, R44.1, SJ3.3
I_C: R45.1, R46.1, SJ4.3
I_PHASE_A: ACS1.3 (IP-_1), ACS1.4 (IP-_2), PAD3.1
I_PHASE_B: ACS2.3 (IP-_1), ACS2.4 (IP-_2), PAD4.1
I_PHASE_C: ACS3.3 (IP-_1), ACS3.4 (IP-_2), PAD5.1
I_SENSE: JP22.P$6 (6), R23.1, R24.1
MOT_TEMP: JP22.P$8 (8)
unnamed: IC4.7 (HO), R11.1
unnamed: IC3.7 (HO), R7.1
unnamed: ACS712.7 (VIOUT), R23.2
unnamed: IC3.5 (LO), R8.1
unnamed: Q1.1 (G), R7.2
unnamed: C1.+, D1.1 (C), IC3.8 (VB)
unnamed: IC4.5 (LO), R12.1
unnamed: Q3.1 (G), R11.2
unnamed: Q5.1 (G), R15.2
unnamed: C2.+, D2.1 (C), IC4.8 (VB)
unnamed: Q6.1 (G), R16.2
unnamed: IC5.7 (HO), R15.1
unnamed: IC5.5 (LO), R16.1
unnamed: C3.+, D3.1 (C), IC5.8 (VB)
unnamed: ACS712.6 (FILTER), C11.1
unnamed: C43.2, IC7.1 (C1-)
unnamed: C44.2, IC7.3 (C2-)
unnamed: C43.1, IC7.2 (C1+)
unnamed: C44.1, IC7.4 (C2+)
unnamed: ACS1.6 (FILTER), C20.1
unnamed: ACS1.7 (VIOUT), R41.2
unnamed: ACS2.6 (FILTER), C23.1
unnamed: ACS2.7 (VIOUT), R43.2
unnamed: ACS3.6 (FILTER), C26.1
unnamed: ACS3.7 (VIOUT), R45.2
unnamed: Q2.1 (G), R8.2
unnamed: Q4.1 (G), R12.2
NC: JP22.P$10 (10)
PHASE_A: ACS1.1 (IP+_1), ACS1.2 (IP+_2), C1.-, IC3.6 (VS), Q1.3 (S), Q2.2 (D), R17.1
PHASE_B: ACS2.1 (IP+_1), ACS2.2 (IP+_2), C2.-, IC4.6 (VS), Q3.3 (S), Q4.2 (D), R19.1
PHASE_C: ACS3.1 (IP+_1), ACS3.2 (IP+_2), C3.-, IC5.6 (VS), Q5.3 (S), Q6.2 (D), R21.1
PS_ID: JP22.P$5 (5), R1.1, R2.2
TEMP: JP22.P$7 (7)
VBD: C4.+, C28.1, C29.1, C30.1, IC3.1 (VCC), IC4.1 (VCC), IC5.1 (VCC), SJ10.2
VBD_PUMP: C45.1, C46.+, IC7.6 (VOUT), SJ10.3
V_BATT: JP22.P$9 (9), R26.1, R27.2

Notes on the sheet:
Phase Drivers
License: CC-BY-SA 3.0 DE
http://creativecommons.org/licenses/by-sa/3.0/de/
Commutation detection
open-bldc (C) 2008-2009 Piotr Esden-Tempski <piotr at esden.net>
Powerstage

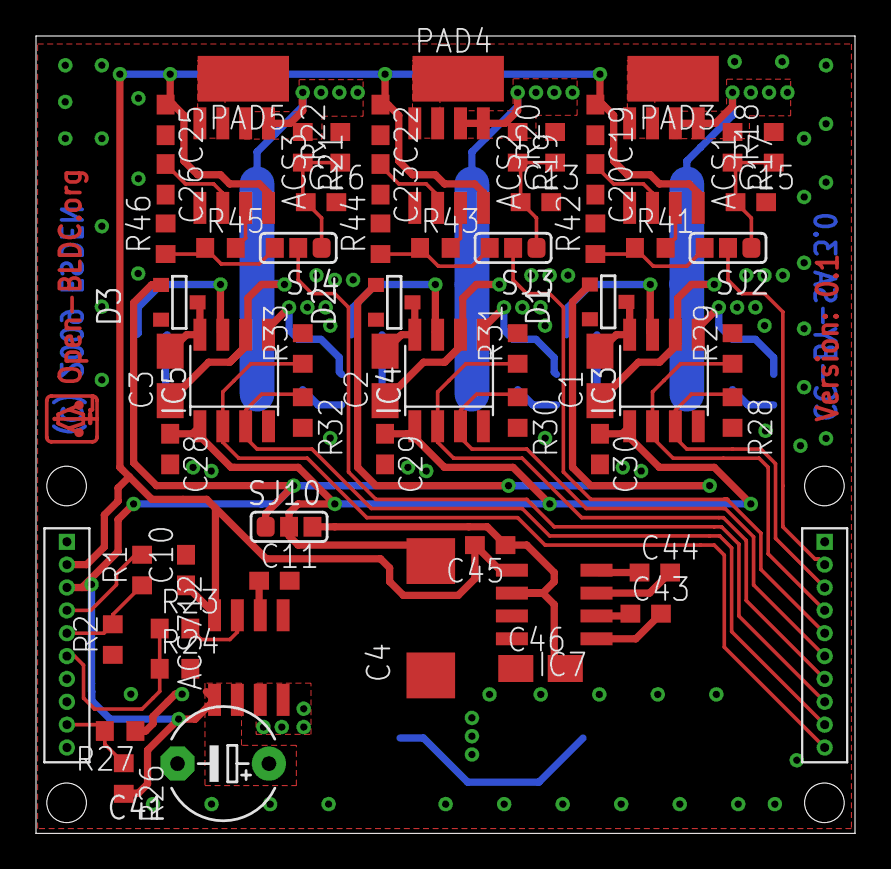
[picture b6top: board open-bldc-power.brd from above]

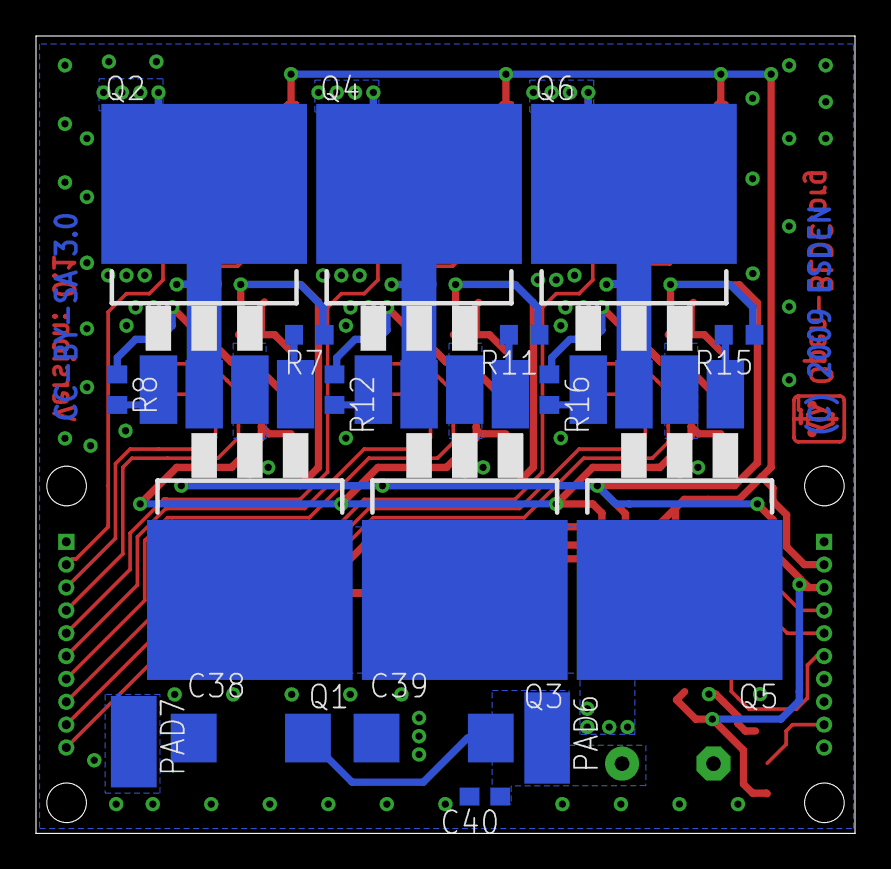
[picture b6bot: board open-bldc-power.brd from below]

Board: 2 copper layers, 45.5 x 44.3 mm, 84 parts (17 on the bottom side), 58 nets.
